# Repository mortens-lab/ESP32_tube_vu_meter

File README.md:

## ESP32 - tube VU meter + misc LED effects

Including Arduino code for ESP32 WROOM module.  <br />
Including three different schematics and 2-layer PCBs designed in KiCad.  <br />
Including three 3D models for parts - designed in Fusion 360.  <br />
Video: https://www.youtube.com .......

<!--  -->
<!-- This content will not appear in the rendered Markdown -->
6 VU meter types:

- Standard Rainbow
- Standard center
- Standard changing Color
- Standard center changing Color
- Shooting Star
- Falling Star

10 LED effects:

- Snowflakes
- Ripple
- Ripple with background
- Twinkle
- Twinkle random Colors
- Fire
- Rainbow
- Water Drops
- Bouncing Balls
- All white

Have fun, I hope you learned something new :-)

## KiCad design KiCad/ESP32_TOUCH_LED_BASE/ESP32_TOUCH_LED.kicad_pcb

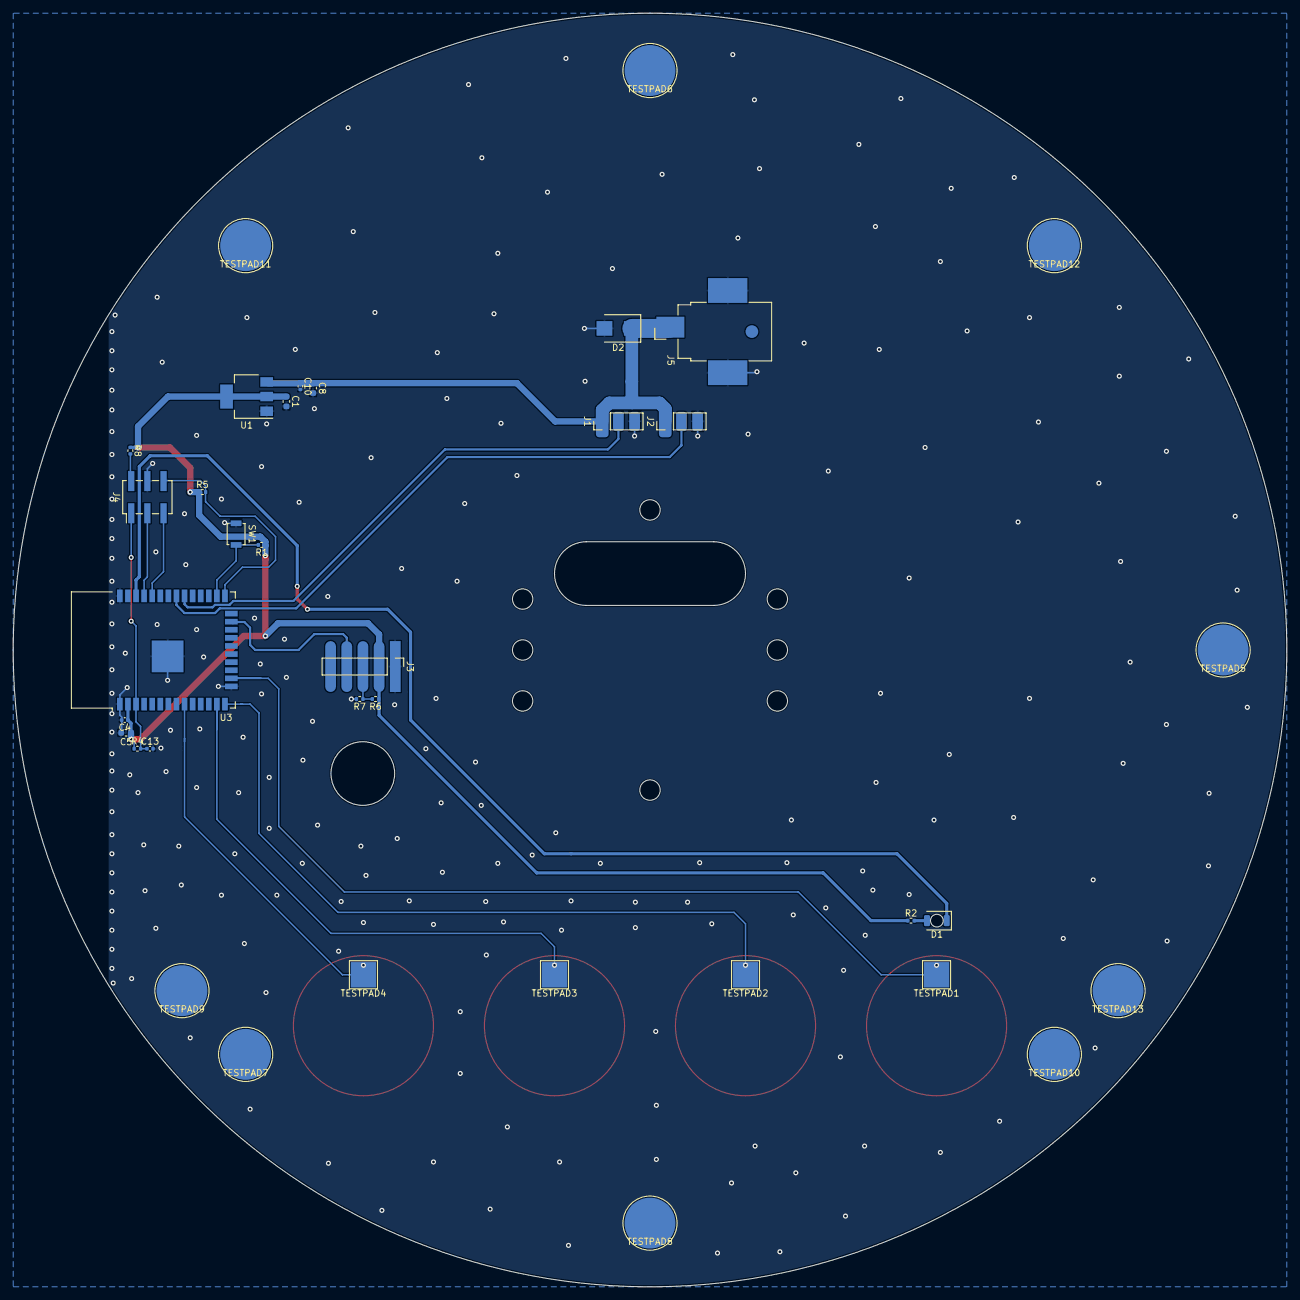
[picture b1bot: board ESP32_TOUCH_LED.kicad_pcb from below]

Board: 2 copper layers, 200.0 x 200.0 mm, 36 parts (36 on the bottom side), 19 nets.

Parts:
C1, C8: 10u/10V; C_0603_1608Metric
C4, C10, C13: 100n; C_0402_1005Metric
C5: 1u; C_0603_1608Metric
D1: LED_Small; LED_1206_3216Metric_ReverseMount_Hole1.8x2.4mm
D2: SMBJ5.0; D_SMB
J1, J2: Conn_01x03; PinHeader_1x03_P2.54mm_Vertical
J3: Conn_01x05; PinHeader_1x05_P2.54mm_Vertical
J4: Conn_02x03_Odd_Even; PinHeader_2x03_P2.54mm_Vertical_SMD
J5: Barrel_Jack_Switch; BarrelJack_CUI_PJ-036AH-SMT_Horizontal
R1: 2K2; R_0402_1005Metric
R2, R4, R5: 1K; R_0402_1005Metric
R6, R7, R8: 0R; R_0402_1005Metric
SW1: SW_SPST; SW_SPST_B3U-1000P
TESTPAD1, TESTPAD2, TESTPAD3, TESTPAD4: TESTPAD; TestPoint_Pad_4.0x4.0mm
TESTPAD5, TESTPAD6, TESTPAD7, TESTPAD8, TESTPAD9, TESTPAD10, TESTPAD11, TESTPAD12, TESTPAD13: TESTPAD; TestPoint_Pad_D8.0mm
U1: LM1117-3.3; SOT-223-3_TabPin2
U3: ESP32-WROOM-32D; ESP32-WROOM-32

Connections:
+3V3: C1.1, C4.1, C5.1, J3.2, R1.1, R2.1, R4.1, R5.1, R6.1, R8.1, U1.2, U3.2
+5V: C8.1, C10.1, D2.1, J1.1, J2.1, J5.1, U1.3
/ESP_EN: C13.1, J4.1, R4.2, U3.3
/ESP_IO0: J4.6, R5.2, U3.25
/ESP_RXD: J4.5, U3.34
/ESP_TXD: J4.3, U3.35
/LED_ON: D1.1, U3.36
/LED_WS2812B_1: J1.2, U3.30
/LED_WS2812B_2: J2.2, U3.31
/MIC: J3.4, U3.23
/SW: R1.2, SW1.2, U3.26
/TOUCH_BRIGHT_DN: TESTPAD3.1, U3.13
/TOUCH_BRIGHT_UP: TESTPAD2.1, U3.14
/TOUCH_MODE_UP: TESTPAD4.1, U3.9
/TOUCH_ON: TESTPAD1.1, U3.16
GND: C1.2, C4.2, C5.2, C8.2, C10.2, C13.2, D2.2, J1.3, J2.3, J3.1, J4.4, J5.2, J5.3, R7.2, SW1.1, TESTPAD5.1, TESTPAD6.1, TESTPAD7.1, TESTPAD8.1, TESTPAD9.1, TESTPAD10.1, TESTPAD11.1, TESTPAD12.1, TESTPAD13.1, U1.1, U3.1, U3.15, U3.38, U3.39
unnamed: D1.2, R2.2
unnamed: J3.3, R6.2, R7.1
unnamed: J4.2, R8.2

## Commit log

2021-10-24 Create LICENSE
